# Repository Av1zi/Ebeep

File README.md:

# Ebeep

Two handheld wireless devices that can message each other and play games, built as a personal gift.

> **E** for eInk. **Beep** for beeper

---

## Project Showcase

### 3D render

https://github.com/user-attachments/assets/bd9d271b-df7e-4e4d-8fb2-d193bfb4d486

### Walkthrough
https://github.com/user-attachments/assets/030f00d7-5b2a-4592-a6ae-74eca7de7010

---

## Features

- **Messaging** - 3-button scrollable alphabet, double-space to send
- **Games** - TicTacToe, Connect 4, and Blackjack
- **E-Ink display** - 2.9" screen
- **Battery powered** - USB-C charging
- **Deep sleep** - sleeps when you're not using it to save battery
- **Works anywhere with WiFi** - the two devices talk over MQTT, so they don't need to be near each other

---

## Hardware

| Component | Part |
|---|---|
| Microcontroller | Seeed XIAO ESP32-C6 |
| Display | WeAct 2.9" eInk |
| Battery | 3.7V LiPo, 3000mAh |
| Buttons | 3× low profile mechanical keyboard switches |
| Case | ~76g PLA, 4× M4 heated inserts, 4× M4×25 screws |
| Other | 2× 200kΩ resistors, 5×7cm perfboard |

---

## How It Works

### Communication
Both devices connect to WiFi and talk through an MQTT broker (I used the free HiveMQ Cloud tier). Each device listens on its own topic and publishes to the other one's.

### WiFi Setup
When the device wakes up and none of its known networks are in range, it opens a hotspot (`Ebeep_1_config` or `Ebeep_2_config`). Connect to it from any phone/pc and a setup page pops up automatically, there you will have to enter the wifi details and press done. (to save battery the hotspot will close by itself after 5 minutes) The device remembers up to 5 networks and picks whichever one is in range.

Walkthrough:

https://github.com/user-attachments/assets/75ae72dc-5833-4c83-8c6c-1c9a049145ae

### Typing Interface
- **Left / Right** - scroll through characters (`SPC A B C ... Z . ! ? <3`)
- **Select** - confirm the current character
- **Two spaces in a row** - send the message
- **DEL on empty** - exit compose

### Games
- **TicTacToe** - classic 3×3. Whoever starts the match first goes first.
- **Connect 4** - 7×6 grid, pieces drop with gravity.
- **Blackjack** - single player (the only one that doesn't need the other device). Dealer stands on soft 17.

### Power Management
The beeper goes to sleep if you don't use it for 10 minutes (you can change this in `config.h`). While asleep it disconnects from WiFi and the MQTT server and basically shuts off to save battery.

Wake it by pressing the left or middle button. On wake-up it looks for a network it remembers, and if it can't find one it starts its own hotspot so you can set up WiFi again (see WiFi Setup).

---

## PCB

A custom PCB has been fully designed and routed in KiCad to replace the hand-wired perfboard build. It's not ordered or fabricated yet, so the build instructions below are still perfboard based. The PCB is a planned upgrade for a future revision.

> [!WARNING]
> The PCB has not been fitted or tested against the case files in this repo. If you order it, expect to redesign the case (or at least the mounting points) to fit. It is **not** a drop-in replacement yet.

---

## Building Your Own

### Print Settings
I used the printer default settings, with tree supports. I have a multi-nozzle printer so I used a support interface layer for a cleaner surface, but it's not necessary.

### Electrical Diagram

### Building Instructions
1. 3D print the files from the `CAD/STL` folder
2. Solder everything onto the perfboard following the electrical diagram above
3. Flash the code (see **Setting Up the Code** below) and test before closing the case
4. Fit the components into the case and put double-sided tape under the battery to hold it
5. Press in the 4× M4 heated inserts, then screw the case shut with the M4 screws

### Setting Up the Code
1. In `include/config.h` change `DEVICE_NUM` to `1` on one device and `2` on the other
2. Copy `include/secret.example.h` to `include/secret.h` and fill in your MQTT broker credentials (`secret.h` is gitignored so it stays private)
3. Upload via PlatformIO. The `huge_app.csv` partition scheme is required
4. On first boot, connect to the config hotspot (`Ebeep_1_config` or `Ebeep_2_config`) and enter your WiFi credentials

---

## License

GPL 3.0 - Do whatever you want with it, just keep it open source as well.

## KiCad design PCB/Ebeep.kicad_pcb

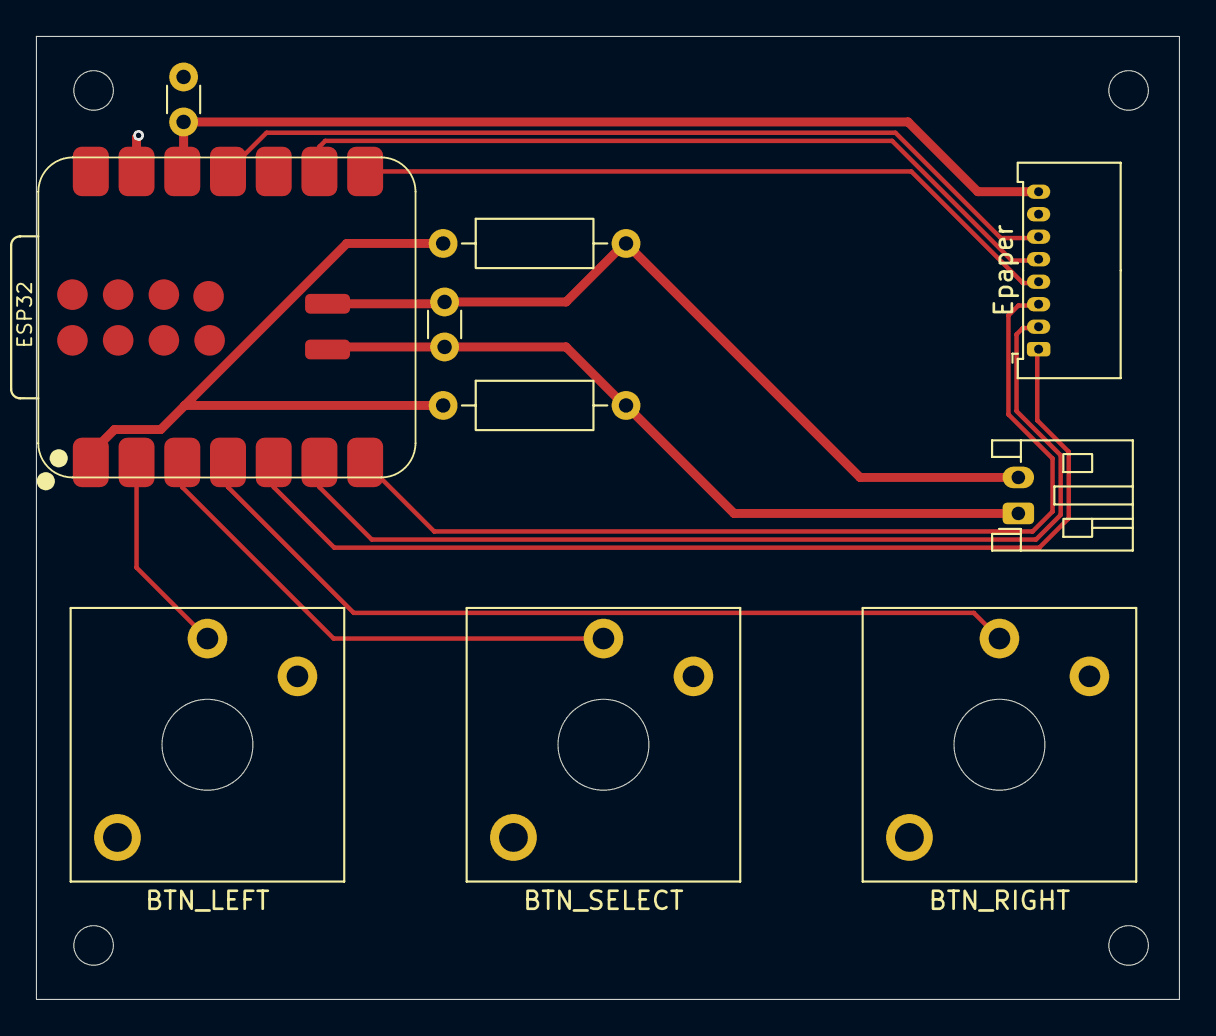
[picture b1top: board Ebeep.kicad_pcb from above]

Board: 2 copper layers, 63.5 x 53.5 mm, 10 parts (0 on the bottom side), 14 nets.

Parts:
BTN_LEFT: SW_Push; SW_Kailh_Choc_V2_1.00u
BTN_RIGHT: SW_Push; SW_Kailh_Choc_V2_1.00u
BTN_SELECT: SW_Push; SW_Kailh_Choc_V2_1.00u
C1, C2: 100nF; C_Disc_D3.0mm_W1.6mm_P2.50mm
ESP32: XIAO-ESP32-C6-SMD
Epaper: WeAct 2.9" ePaper; Molex_PicoBlade_53048-0810_1x08_P1.25mm_Horizontal
JST-PH-2pin1: Conn_01x02; JST_PH_S2B-PH-K_1x02_P2.00mm_Horizontal
R1, R2: 200K; R_Axial_DIN0207_L6.3mm_D2.5mm_P10.16mm_Horizontal

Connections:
/+BATT: C1.1, ESP32.23 (VBAT), JST-PH-2pin1.1, R1.2
/-BATT: C1.2, ESP32.24 (GND), JST-PH-2pin1.2, R2.2
/BUSY: ESP32.5 (D4), Epaper.1
/CS: ESP32.8 (D7), Epaper.4
/D/C: ESP32.7 (D6), Epaper.3
/GND: BTN_LEFT.2, BTN_RIGHT.2, BTN_SELECT.2, C2.1, ESP32.13 (GND), Epaper.7
/RES: ESP32.6 (D5), Epaper.2
/SCL: ESP32.9 (D8), Epaper.5
/SDA: ESP32.11 (D10), Epaper.6
/VCC: C2.2, ESP32.12 (3V3_OUT), Epaper.8
unnamed: ESP32.1 (D0), R1.1, R2.1
unnamed: BTN_LEFT.1, ESP32.2 (D1)
unnamed: BTN_SELECT.1, ESP32.3 (D2)
unnamed: BTN_RIGHT.1, ESP32.4 (D3)

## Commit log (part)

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2026-06-01 first Upload
2026-06-01 aaaa
2026-06-01 UI v0.1
2026-06-02 readme file
2026-06-03 made the UI way better
2026-06-03 organized the files
    looks much better ngl
2026-06-04 WIFI
2026-06-04 Fix gitignore path and untrack secret.h
2026-06-08 GameSelect menu
    ART ISNT DONE BY ME ITS A PLACE HOLDER!!
2026-06-09 updated to esp32
2026-06-09 Revise Ebeep project description in README
    Updated project description for clarity and conciseness.
2026-06-10 added wifi support and fixed a couple of bugs
2026-06-11 added mqtt
2026-06-11 optimized code (by claude)
2026-06-19 tic tac toe major overhall
    added a lot of shit as well fixed bugs and tried to make compase state better
2026-06-20 added wifi icons and cad files to project
    + fixed bugs
2026-06-21 tic tac toe working
    updated model for M4 screws
2026-06-30 battary readout
